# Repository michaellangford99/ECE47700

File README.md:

# ECE47700

Placeholder for eventual Github Pages display of course information

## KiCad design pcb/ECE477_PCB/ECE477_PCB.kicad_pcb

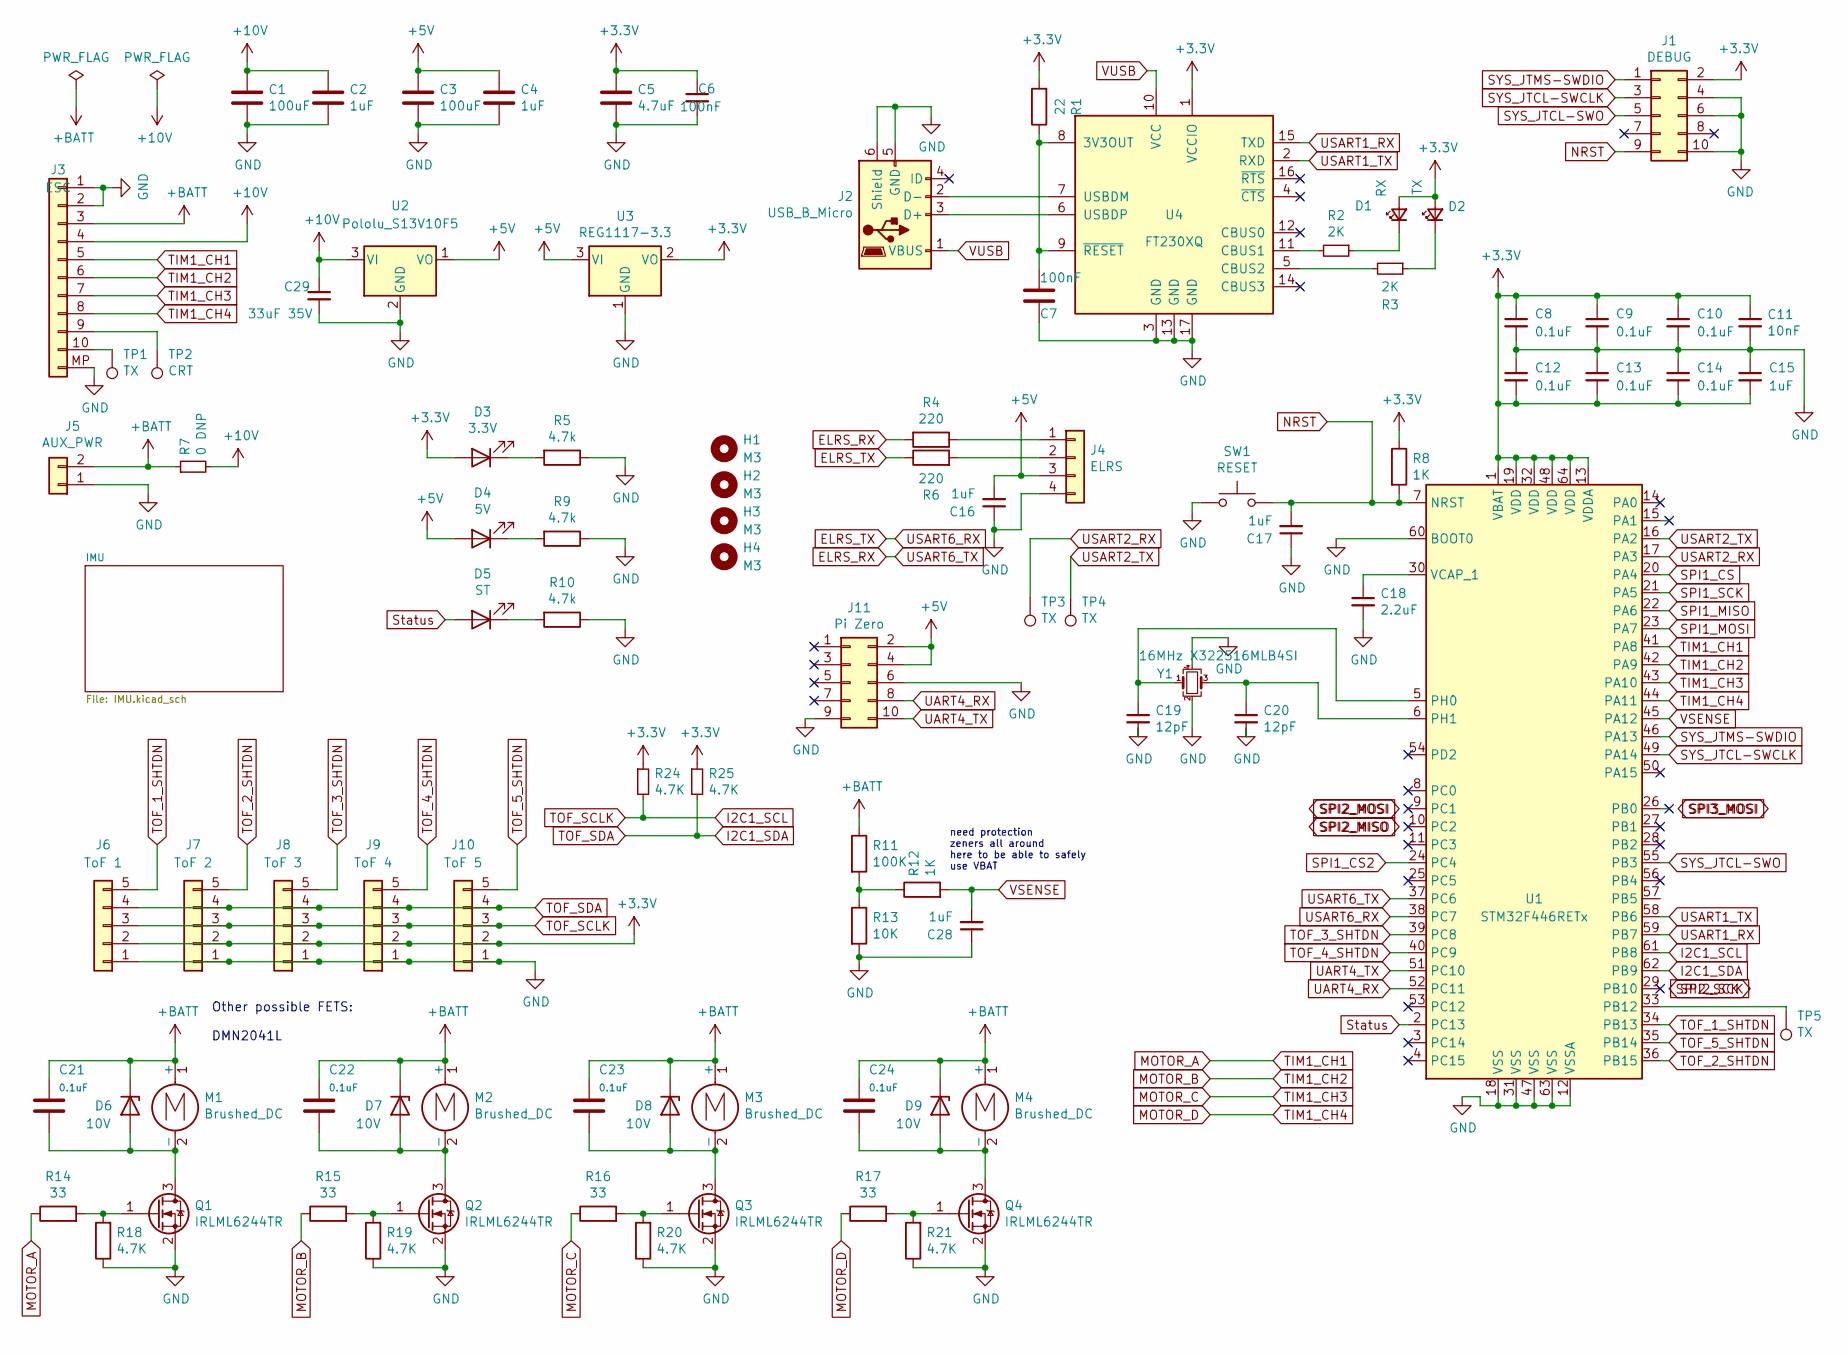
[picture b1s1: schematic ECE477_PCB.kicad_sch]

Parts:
C1, C3: 100uF; C_Elec_3x5.4; JLCPCB BOM 0
C2, C4, C15, C16, C17, C28: 1uF; C_0603_1608Metric; LCSC Part # C15849
C5: 4.7uF; C_1210_3225Metric; JLCPCB BOM 0
C6, C7: 100nF; C_0402_1005Metric; LCSC Part # C1525
C8, C9, C10, C12, C13, C14: 0.1uF; C_0603_1608Metric
C11: 10nF; C_0603_1608Metric; LCSC Part # C57112
C18: 2.2uF; C_0603_1608Metric; LCSC Part # C23630
C19, C20: 12pF; C_0603_1608Metric; LCSC Part # C38523
C21, C22, C23, C24: 0.1uF; C_0402_1005Metric; LCSC Part # C1525
C29: 33uF 35V; C_1206_3216Metric
D1: RX; LED_0603_1608Metric; LCSC Part # C72041
D2: TX; LED_0603_1608Metric; LCSC Part # C2286
D3: 3.3V; LED_0603_1608Metric; LCSC Part # C72038
D4: 5V; LED_0603_1608Metric; LCSC Part # C72038
D5: ST; LED_0603_1608Metric; LCSC Part # C72043
D6, D7, D8, D9: 10V; D_0805_2012Metric; JLCPCB BOM 0
H1, H2, H3, H4: M3; MountingHole_3.2mm_M3
J1: DEBUG; PinSocket_2x05_P1.27mm_Vertical_SMD; JLCPCB BOM 0
J2: USB_B_Micro; USB_Micro-B_Molex-105017-0001; JLCPCB BOM 0
J3: ESC; JST_SH_SM10B-SRSS-TB_1x10-1MP_P1.00mm_Horizontal
J4: ELRS; PinSocket_1x04_P1.27mm_Vertical; JLCPCB BOM 0
J5: AUX_PWR; PinHeader_1x02_P2.54mm_Vertical; JLCPCB BOM 0
J6: ToF 1; PinHeader_1x05_P1.00mm_Vertical
J7: ToF 2; PinHeader_1x05_P1.00mm_Vertical
J8: ToF 3; PinHeader_1x05_P1.00mm_Vertical
J9: ToF 4; PinHeader_1x05_P1.00mm_Vertical
J10: ToF 5; PinHeader_1x05_P1.00mm_Vertical
J11: Pi Zero; PinHeader_2x05_P2.54mm_Vertical; JLCPCB BOM 0
M1, M2, M3, M4: Brushed_DC; PinHeader_1x02_P2.00mm_Vertical; JLCPCB BOM 0
Q1, Q2, Q3, Q4: IRLML6244TR; SOT-23_Handsoldering; JLCPCB BOM 0
R1: 22; R_0402_1005Metric; LCSC Part # C25092
R2, R3: 2K; R_0603_1608Metric; LCSC Part # C22975
R4, R6: 220; R_0603_1608Metric; LCSC Part # C22962
R5, R9, R10: 4.7k; R_0603_1608Metric; LCSC Part # C23162
R7: 0 DNP; R_0603_1608Metric; LCSC Part # C23162
R8: 1K; R_0603_1608Metric; LCSC Part # C21190
R11: 100K; R_0603_1608Metric; LCSC Part # C22984
R12: 1K; R_0603_1608Metric; LCSC Part # C22984
R13: 10K; R_0603_1608Metric; LCSC Part # C25803
R14, R15, R16, R17: 33; R_0603_1608Metric; LCSC Part # C23140
R18, R19, R20, R21, R24, R25: 4.7K; R_0603_1608Metric; LCSC Part # C23162
SW1: RESET; SW_SPST_B3U-1000P; JLCPCB BOM 0
TP1, TP3, TP4, TP5: TX; TestPoint_Pad_D1.0mm
TP2: CRT; TestPoint_Pad_D1.0mm
U1: STM32F446RETx; LQFP-64_10x10mm_P0.5mm; LCSC Part # C69336
U2: Pololu_S13V10F5; PinHeader_1x03_P2.54mm_Horizontal
U3: REG1117-3.3; SOT-223
U4: FT230XQ; QFN-16-1EP_4x4mm_P0.65mm_EP2.5x2.5mm; LCSC Part # C128629
Y1: 16MHz X322516MLB4SI; Crystal_SMD_3225-4Pin_3.2x2.5mm; LCSC Part # C13738

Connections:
+3V3: C5.1, C6.1, C8.1, C9.1, C10.1, C11.1, C12.2, C13.2, C14.2, C15.2, D1.2 (A), D2.2 (A), D3.2 (A), J1.2, J6.2, J7.2, J8.2, J9.2, J10.2, R1.2, R8.1, R24.1, R25.1, U1.1 (VBAT), U1.13 (VDDA), U1.19 (VDD), U1.32 (VDD), U1.48 (VDD), U1.64 (VDD), U3.2 (VO), U4.1 (VCCIO); also elsewhere on the board
+5V: C3.1, C4.1, C16.2, D4.2 (A), J4.3, J11.2, J11.4, U2.1 (VO), U3.3 (VI)
+10V: C1.1, C2.1, C29.1, J3.4, R7.2, U2.3 (VI)
+BATT: C21.1, C22.1, C23.1, C24.1, D6.1 (K), D7.1 (K), D8.1 (K), D9.1 (K), J3.3, J5.2, M1.1 (+), M2.1 (+), M3.1 (+), M4.1 (+), R7.1, R11.1
ELRS_RX: R4.2, U1.37 (PC6)
ELRS_TX: R6.1, U1.38 (PC7)
GND: C1.2, C2.2, C3.2, C4.2, C5.2, C6.2, C7.1, C8.2, C9.2, C10.2, C11.2, C12.1, C13.1, C14.1, C15.1, C16.1, C17.1, C18.2, C19.2, C20.2, C28.1, C29.2, J1.4, J1.6, J1.10, J2.5 (GND), J2.6 (Shield), J3.1, J3.2, J3.MP (Pin_11), J4.4, J5.1, J6.1, J7.1, J8.1, J9.1, J10.1, J11.6, J11.9, Q1.2 (S), Q2.2 (S), Q3.2 (S), Q4.2 (S), R5.1, R9.1, R10.1, R13.2, R18.1, R19.1, R20.1, R21.1, SW1.1, U1.12 (VSSA), U1.18 (VSS), U1.31 (VSS), U1.47 (VSS), U1.60 (BOOT0), U1.63 (VSS), U2.2 (GND), U3.1 (GND), U4.3 (GND), U4.13 (GND), U4.17 (GND), Y1.2, Y1.4; also elsewhere on the board
I2C1_SCL: J6.3, J7.3, J8.3, J9.3, J10.3, R24.2, U1.61 (PB8)
I2C1_SDA: J6.4, J7.4, J8.4, J9.4, J10.4, R25.2, U1.62 (PB9)
MOTOR_A: J3.5, R14.1, U1.41 (PA8)
MOTOR_B: J3.6, R15.1, U1.42 (PA9)
MOTOR_C: J3.7, R16.1, U1.43 (PA10)
MOTOR_D: J3.8, R17.1, U1.44 (PA11)
NRST: C17.2, J1.9, R8.2, SW1.2, U1.7 (NRST)
unnamed: C7.2, R1.1, U4.8 (3V3OUT), U4.9 (~RESET)
unnamed: C18.1, U1.30 (VCAP_1)
unnamed: C19.1, U1.5 (PH0), Y1.1
unnamed: C20.1, U1.6 (PH1), Y1.3
unnamed: C21.2, D6.2 (A), M1.2 (-), Q1.3 (D)
unnamed: C22.2, D7.2 (A), M2.2 (-), Q2.3 (D)
unnamed: C23.2, D8.2 (A), M3.2 (-), Q3.3 (D)
unnamed: C24.2, D9.2 (A), M4.2 (-), Q4.3 (D)
unnamed: D1.1 (K), R2.1
unnamed: D2.1 (K), R3.1
unnamed: D3.1 (K), R5.2
unnamed: D4.1 (K), R9.2
unnamed: D5.1 (K), R10.2
unnamed: J2.2 (D-), U4.7 (USBDM)
unnamed: J2.3 (D+), U4.6 (USBDP)
unnamed: J3.9, TP2.1
unnamed: J3.10, TP1.1
unnamed: J4.1, R4.1
unnamed: J4.2, R6.2
unnamed: Q1.1 (G), R14.2, R18.2
unnamed: Q2.1 (G), R15.2, R19.2
unnamed: Q3.1 (G), R16.2, R20.2
unnamed: Q4.1 (G), R17.2, R21.2
unnamed: R2.2, U4.11 (CBUS1)
unnamed: R3.2, U4.5 (CBUS2)
unnamed: R11.2, R12.1, R13.1
unnamed: TP5.1, U1.33 (PB12)
SPI1_CS: U1.20 (PA4); also elsewhere on the board
SPI1_CS2: U1.24 (PC4); also elsewhere on the board
SPI1_MISO: U1.22 (PA6); also elsewhere on the board
SPI1_MOSI: U1.23 (PA7); also elsewhere on the board
SPI1_SCK: U1.21 (PA5); also elsewhere on the board
SYS_JTCL-SWCLK: J1.3, U1.49 (PA14)
SYS_JTCL-SWO: J1.5, U1.55 (PB3)
SYS_JTMS-SWDIO: J1.1, U1.46 (PA13)
Status: D5.2 (A), U1.2 (PC13)
TOF_1_SHTDN: J6.5, U1.34 (PB13)
TOF_2_SHTDN: J7.5, U1.36 (PB15)
TOF_3_SHTDN: J8.5, U1.39 (PC8)
TOF_4_SHTDN: J9.5, U1.40 (PC9)
TOF_5_SHTDN: J10.5, U1.35 (PB14)
UART4_RX: J11.8, U1.52 (PC11)
UART4_TX: J11.10, U1.51 (PC10)
USART1_RX: U1.59 (PB7), U4.15 (TXD)
USART1_TX: U1.58 (PB6), U4.2 (RXD)
USART2_RX: TP3.1, U1.17 (PA3)
USART2_TX: TP4.1, U1.16 (PA2)
VSENSE: C28.2, R12.2, U1.45 (PA12)
VUSB: J2.1 (VBUS), U4.10 (VCC)

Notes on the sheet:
need protection zeners all around here to be able to safely use VBAT
Other possible FETS: DMN2041L

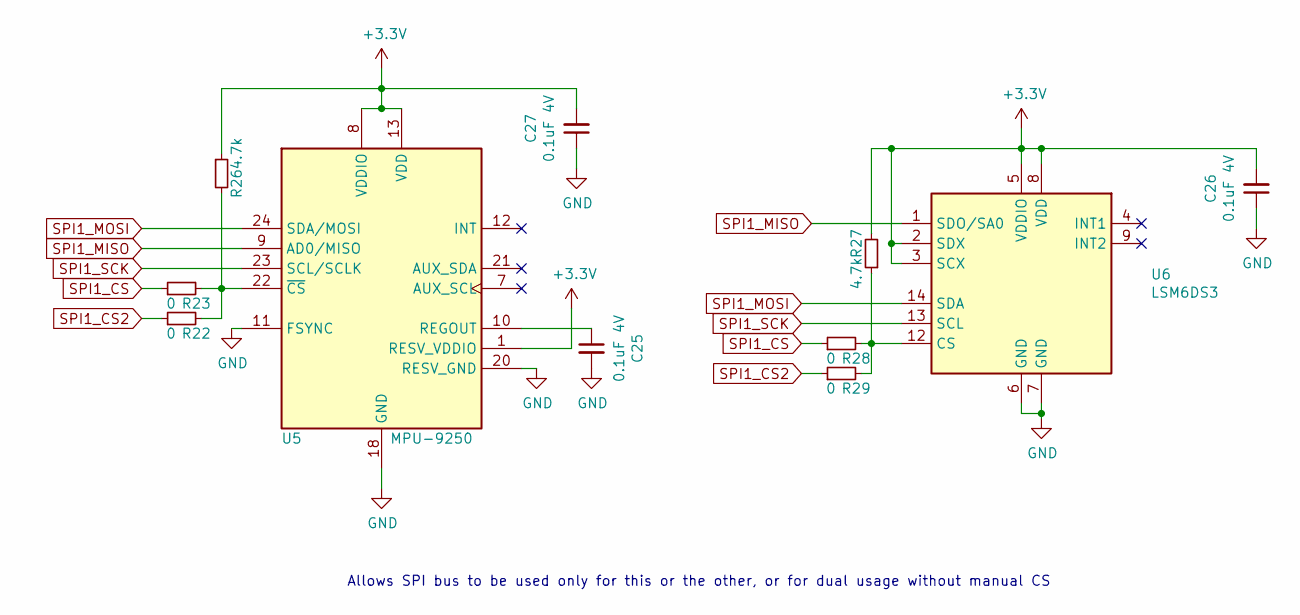
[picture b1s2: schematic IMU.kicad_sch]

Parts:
C25, C26, C27: 0.1uF 4V; C_0603_1608Metric; LCSC Part # C1525
R22, R23, R28, R29: 0; R_0603_1608Metric; LCSC Part # C23162
R26, R27: 4.7k; R_0603_1608Metric
U5: MPU-9250; InvenSense_QFN-24_3x3mm_P0.4mm
U6: LSM6DS3; LGA-14_3x2.5mm_P0.5mm_LayoutBorder3x4y

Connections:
+3V3: C26.2, C27.2, R26.1, R27.2, U5.1 (RESV_VDDIO), U5.8 (VDDIO), U5.13 (VDD), U6.2 (SDX), U6.3 (SCX), U6.5 (VDDIO), U6.8 (VDD); also elsewhere on the board
GND: C25.2, C26.1, C27.1, U5.11 (FSYNC), U5.18 (GND), U5.20 (RESV_GND), U6.6 (GND), U6.7 (GND); also elsewhere on the board
unnamed: C25.1, U5.10 (REGOUT)
unnamed: R22.2, R23.2, R26.2, U5.22 (~CS)
unnamed: R27.1, R28.2, R29.2, U6.12 (CS)
SPI1_CS: R23.1, R28.1; also elsewhere on the board
SPI1_CS2: R22.1, R29.1; also elsewhere on the board
SPI1_MISO: U5.9 (AD0/MISO), U6.1 (SDO/SA0); also elsewhere on the board
SPI1_MOSI: U5.24 (SDA/MOSI), U6.14 (SDA); also elsewhere on the board
SPI1_SCK: U5.23 (SCL/SCLK), U6.13 (SCL); also elsewhere on the board

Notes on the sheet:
Allows SPI bus to be used only for this or the other, or for dual usage without manual CS

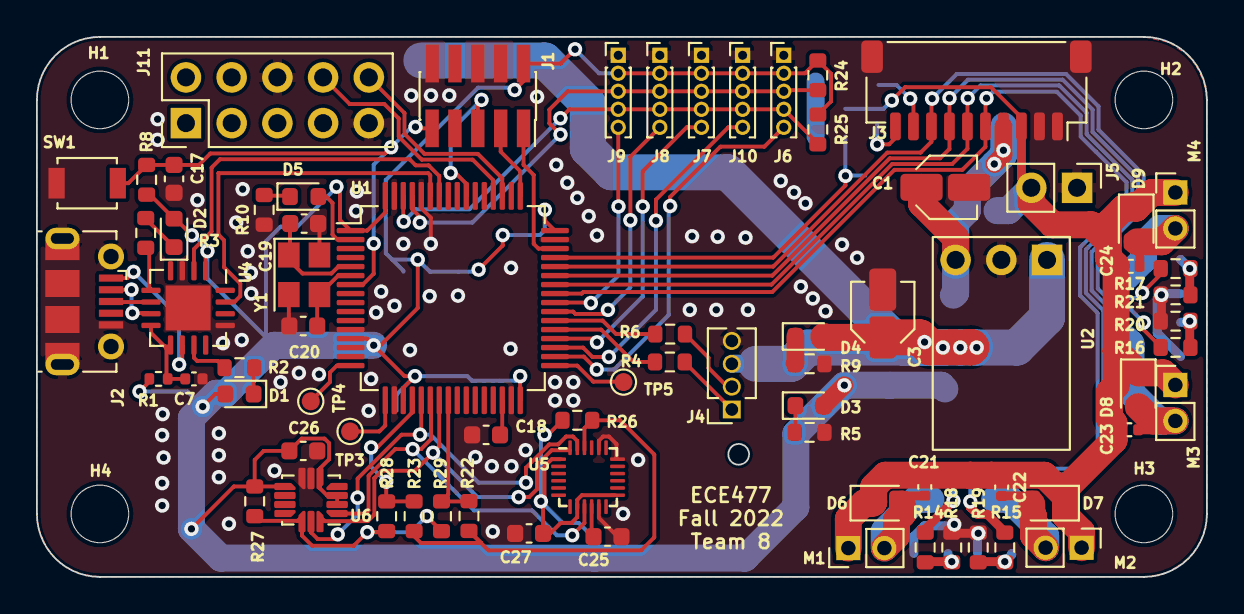
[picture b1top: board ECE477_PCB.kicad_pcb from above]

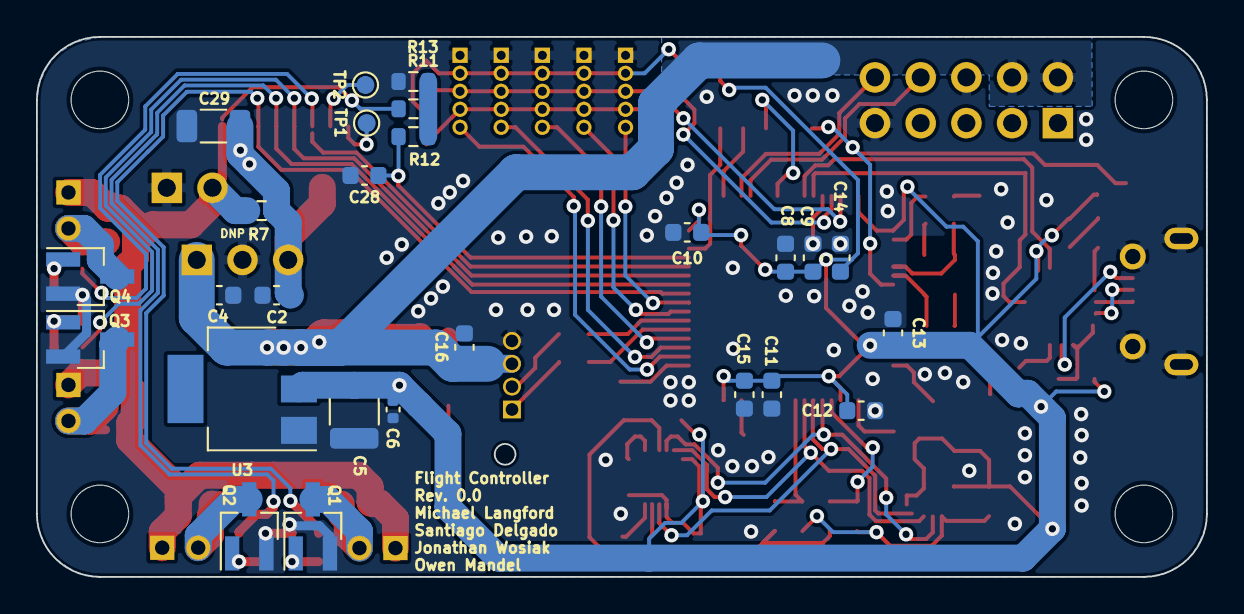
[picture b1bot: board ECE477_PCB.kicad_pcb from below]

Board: 2 copper layers, 65.0 x 30.0 mm, 103 parts (26 on the bottom side), 66 nets.

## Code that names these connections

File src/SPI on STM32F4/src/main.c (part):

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
void init_UART(void){
        //USART1
        //PB6, PB7

        //Enable GPIOB
        RCC->AHB1ENR |= RCC_AHB1ENR_GPIOBEN;

        //zero out AFR for PB6 and PB7
        GPIOB->AFR[0] &= ~(0xF << (6 *4));
        GPIOB->AFR[0] &= ~(0xF << (7 *4));

        //select AF7 for PB6 and7PB6 as USART1_TX and USART1_RX, respectively
        GPIOB->AFR[0] |= (0x07 << (6 *4));
        GPIOB->AFR[0] |= (0x07 << (7 *4));

        //zero out MODER for PB6 and PB7
        GPIOB->MODER &= ~(0xf << 12);
        //select alternate function mode for PB6 and PB7
        GPIOB->MODER |= (10 << 12);


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	RCC -> AHB1ENR |= RCC_AHB1ENR_GPIOAEN;
    RCC -> APB2ENR |= RCC_APB2ENR_SPI1EN;

    //using pins PA4-PA7
    GPIOA -> MODER &= ~0x0000ff00;
    GPIOA -> MODER |= 0x0000a900;

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    GPIOA -> AFR[0] &= ~0xfff00000;
    GPIOA -> AFR[0] |= 0x55500000;

    //Very high speed GPIO PA4 with a pullup resistor for CS
    //GPIOA -> OSPEEDR |= 0x0000ff00;
    GPIOA -> PUPDR |= 0x00000200;
    GPIOA -> ODR |= (1 << 4);
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
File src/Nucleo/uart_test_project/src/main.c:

/**
  ******************************************************************************
  * @file    main.c
  * @author  Ac6
  * @version V1.0
  * @date    01-December-2013
  * @brief   Default main function.
  ******************************************************************************
*/


#include "stm32f4xx.h"
#include <stdio.h>

#include "fifo.h"
#include "tty.h"

#define FIFOSIZE 16
char serfifo[FIFOSIZE];
int seroffset = 0;

void enable_tty_interrupt()
{
	USART2->CR1 |= USART_CR1_RXNEIE;
	USART2->CR3 |= USART_CR3_DMAR;

	NVIC->ISER[0] |= 1 << 29;

	RCC->AHBENR |= RCC_AHBENR_DMA2EN;
	DMA2->RMPCR |= DMA_RMPCR2_CH2_USART5_RX;
	DMA2_Channel2->CCR &= ~DMA_CCR_EN;  // First make sure DMA is turned off

	DMA2->

	DMA2_Channel2->CMAR = (uint32_t)&serfifo;
	DMA2_Channel2->CPAR = (uint32_t)&(USART5->RDR);
	DMA2_Channel2->CNDTR = FIFOSIZE;
	DMA2_Channel2->CCR &= ~DMA_CCR_DIR;
	DMA2_Channel2->CCR &= ~DMA_CCR_HTIE;
	DMA2_Channel2->CCR &= ~DMA_CCR_TCIE;
	DMA2_Channel2->CCR &= ~DMA_CCR_MSIZE;
	DMA2_Channel2->CCR &= ~DMA_CCR_PSIZE;
	DMA2_Channel2->CCR &= ~DMA_CCR_PINC;
	DMA2_Channel2->CCR |=  DMA_CCR_MINC;
	DMA2_Channel2->CCR |=  DMA_CCR_CIRC;
	DMA2_Channel2->CCR &= ~DMA_CCR_MEM2MEM;
	DMA2_Channel2->CCR |=  DMA_CCR_PL;

	DMA2_Channel2->CCR |= DMA_CCR_EN;
}

int __io_putchar(int c) {
	if (c == '\n') __io_putchar('\r');

	while(!(USART2->SR & USART_SR_TXE)) { }
	USART2->DR = c;
	return c;
}

int interrupt_getchar()
{
	// Wait for a newline to complete the buffer.
	while(!fifo_newline(&input_fifo))
			asm volatile ("wfi"); // wait for an interrupt
	// Return a character from the line buffer.
	char ch = fifo_remove(&input_fifo);
	return ch;
}

int __io_getchar(void) {
	 /*while (!(USART5->ISR & USART_ISR_RXNE)) { }
	 char c = USART5->RDR;
	 return c;*/
	char c = interrupt_getchar();

	return c;
}

void USART2_IRQHandler(void)
{
	while(DMA2_Channel2->CNDTR != sizeof serfifo - seroffset) {
		if (!fifo_full(&input_fifo))
			insert_echo_char(serfifo[seroffset]);
		seroffset = (seroffset + 1) % sizeof serfifo;
	}
}

int main(void)
{
	//USART2
	//PA2, PA3

	//Enable GPIOA
	RCC->AHB1ENR |= RCC_AHB1ENR_GPIOAEN;

	//zero out AFR for PA2 and PA3
	GPIOA->AFR[0] &= ~(0xFF << (2 *4));
	GPIOA->AFR[0] &= ~(0xFF << (3 *4));

	//select AF7 for PA2 and PA3 as USART2_TX and USART2_RX, respectively
	GPIOA->AFR[0] |= (0x07 << (2 *4));
	GPIOA->AFR[0] |= (0x07 << (3 *4));

	//zero out MODER for PA2 and PA3
	GPIOA->MODER &= ~(0xf << 4);

	//select alternate function mode for PA2 and PA3
	GPIOA->MODER |= (10 << 4);

	//Enable USART2
	RCC->APB1ENR |= RCC_APB1ENR_USART2EN;

	USART2->CR1 &= ~USART_CR1_UE;
	USART2->CR1 &= ~(1 << 12);	//set bit 12, 0 for word size 8 bits
	USART2->CR1 &= ~USART_CR1_PCE;				//disable parity control
	USART2->CR2 &= ~USART_CR2_STOP;				//set stop bits to 1

	//ACTUALLY, it seems to be running at 45MHz

	//115_200 = 180MHz / (8 * 2 * USARTDIV)
	//USARTDIV = 180MHZ / (8 * 2 * 115_200)
	//USARTDIV: fraction=0d11, mantissa=0d97
	USART2->BRR = (7) | ((24) << 4);						//set baud rate to 115200

	USART2->CR1 |= USART_CR1_TE;				//enable transmitter
	USART2->CR1 |= USART_CR1_RE;				//enable receiver

	USART2->CR1 |= USART_CR1_UE;				//enable USART


	setbuf(stdin,0);
	setbuf(stdout,0);
	setbuf(stderr,0);



	for(;;) {
		//while (!(u->SR & USART_SR_RXNE)) { }
		//char c = u->DR;
		/*char idx = 0;

		while (text[idx] != 0)
		{
			while(!(u->SR & USART_SR_TXE)) { }
			u->DR = text[idx];
			idx++;
		}
		//USART2->BRR = USART2->BRR + 1;

		GPIOA->ODR ^= 0x1 << 5;
		for (volatile int i = 999999/2; i > 0; i--)
		{
			__asm("NOP");
		}*/
		printf("Enter your name: %d\r\n", 42069);
		/*while (!(u->SR & USART_SR_RXNE)) { }
		char c = u->DR;
		while(!(u->SR & USART_SR_TXE)) { }
		u->DR = c;*/



	}
}

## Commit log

2022-05-18 initial
2022-09-02 added some source files
2022-09-15 removed old files
2022-09-15 added all files
2022-09-23 new source code, additional folders
2022-09-26 created progress rpt, new PCB folder properly named via template use, fixed initial radio text code (it works now)
2022-09-30 added new test project with pwm and motors
2022-09-30 improved formatting works on Nucleo now
2022-09-30 updated PCB to Kicad 6
2022-09-30 found and converted to .wrl 3d model file for connector
2022-10-01 modified layout of motor control and power, added minimal initial schematic for LiDAR and footprints
2022-10-02 updated schematic I2C and UART connections
2022-10-04 getting pretty close. fixed DRC errors, moved UARTS and radio connector, added pi zero connector
2022-10-05 completed first rev of PCB. looks like the Pi connector needs moved slightly, board radius is off but drill positions are still the same
2022-10-05 Non-working SPI code
2022-10-06 modify zero position
2022-10-06 fixed pi zero connector position
2022-10-06 initial rev of LIDAR lib
2022-10-06 switch VL... lib to C
2022-10-06 finished initial port to C
2022-10-07 updated parsing method for receiver, actually verifies the CRC now
2022-10-07 adding last few week's status reports
2022-10-07 renamed datasheet to be more helpful
2022-10-08 fixed ESC connector placement
2022-10-08 adding zip of pcb project for inspection
2022-10-09 VL53L1X.c, main.c, i2c.c
    Changed VL53L1X.c to include our register code
2022-10-09 i2c.h, VL53L1X.h
2022-10-10 further integrated LiDAR library, not all the way there yet
2022-10-11 additional changes
2022-10-11 SysTimeClock
2022-10-11 added new docs
2022-10-11 ignoring huge locla file
2022-10-12 motors running, not the prettiest code yet though
2022-10-13 fixed vias, added test points, fixed ground plane in some spots
2022-10-13 added more datasheets
2022-10-13 now tracking presentation
2022-10-13 fixed more ground plane risks
2022-10-13 fixed potential issues with mounting holes
2022-10-13 updated zip file
2022-10-13 removing old pcb from history
2022-10-13 testing push
2022-10-14 updated powerpoint
2022-10-14 renamed presentation
2022-10-14 updated reqs, block diagram, BOM, added datasheets
2022-10-14 added a couple PCB screenshots
2022-10-14 done
2022-10-14 fixed resistor divider and added keepout under the oscillator
2022-10-18 SPI code (working?)
    work on in ManLab
2022-10-18 added steval
2022-10-19 extended qfn pads, added 3d model
2022-10-20 committing before large change to FTDI
2022-10-20 last fixes, ready to order (I think)
2022-10-20 updated PCB zip file
2022-10-20 ready to order
2022-10-20 zip complete
2022-10-21 purchase version gerbers
2022-10-25 replaced
2022-10-25 replaced pt2
2022-10-25 FULL SPI WORKING Code with UART
2022-10-25 SPI not zipped
2022-10-25 SPI working better
2022-10-25 went full scale, added quick implementation of angle integration and calibration
2022-10-26 adding projects for full board, and for just the LSM6 on the F411. Added systick code with #defines, and modified USART to compute baudrate settings. almost done there.
2022-10-26 got good angle calculation working. Now let's #define everything
2022-10-26 updated cal time. should check for aliasing here
2022-10-26 cleaned up SPI and LSM code with define statements
2022-10-27 "Latest Version Still not operational"
2022-10-29 Hello World
2022-10-30 good data from LIDAR
2022-10-30 adding more code to 477 full project
2022-10-30 updated drivers with better #defines. more to come.
2022-11-01 The color recognition funcitons
2022-11-02 updating pin definitions, adding drivers
2022-11-02 add psuedocode, fix formatting
2022-11-02 getting system working on correct pins. big headache
2022-11-02 motor pwm working on all pins
2022-11-03 got accelerometer working
2022-11-03 got accelerometer working better
2022-11-05 Not finnished but translated to not use arduino library
2022-11-09 added mechanical models and prints
2022-11-10 Finished TMF8801
2022-11-10 temp location for i2c pi code
2022-11-10 Ready to go
2022-11-10 FINAALLYYYgit add I2C_LIDARgit add I2C_LIDAR
2022-11-15 ur mom -santiago
2022-11-16 added docs
2022-11-16 IMU working, all non-nav computer PSSCs met
2022-11-16 added 3D models
2022-11-16 added progress reports
2022-11-17 switched to HSI, PLL to 180MHz, motor PWM and clock constants fixed
2022-11-17 IMU complementary filter working
2022-11-18 updated mount and assembly
2022-11-18 exported new mount stl
2022-11-21 complementary filter fixed, added adaptive gain feature
2022-11-21 untuned, but motors and PID all work
2022-11-26 added decimating FIR option, motor filtering.
2022-11-26 add mpu6500 1st rev, CS pin control in SPI driver
2022-11-29 created common IMU struct, fixed mpu6500 driver, made both work in tandem
2022-11-29 fixed pi uart clock rate, added debug dumps
2022-11-29 moved startup message to usb_uart
2022-11-29 incororated imu updates, changed LPF on motors from loop_rate/256 to loop_rate/64
2022-11-29 added docs and data
2022-11-30 disabled accelerometer filter for noise power estimation
2022-11-30 changed motor decimation, integrating pi uart
2022-11-30 initial pi packet parsing working
2022-12-02 added bounds on each PID response type
2022-12-02 minimal changes to buffer settings
2022-12-02 fixed pi frame format
2022-12-02 safety, radio status, and arming sequence initial code
2022-12-02 added IMU and ESC docs
2022-12-02 TMF8801 lidar sensor working
2022-12-05 fixed and tuned variable complementary filter gain
2022-12-05 working safety code
2022-12-05 autonomous files
2022-12-06 IT FLIES ok now I'll be professional. tuned PIDs, finished mocing code to safety section, reduced LPF on motors
2022-12-09 added I2C lidar, auto-throttle, watchdog, filtering in I2c
2022-12-10 streamlined pulling flight logs off of pi
2022-12-10 first successful auto-throttle flight code
2022-12-10 adding new reports
2022-12-10 updated PID tune, added integral yaw control
2022-12-16 complete merge
2022-12-16 flight log data
2022-12-16 adding lastest progress report
2022-12-16 more docs
2023-01-17 moved test stuff
2023-01-18 added site archive
